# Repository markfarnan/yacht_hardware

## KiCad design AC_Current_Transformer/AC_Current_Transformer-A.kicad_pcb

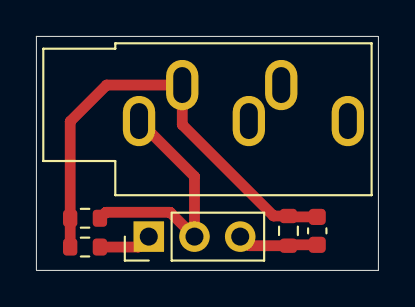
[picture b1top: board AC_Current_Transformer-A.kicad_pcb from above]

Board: 2 copper layers, 19.0 x 13.0 mm, 6 parts (0 on the bottom side), 4 nets.

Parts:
C101: CP; C_0603_1608Metric
J101: AudioJack3; Jack_3.5mm_CUI_SJ1-3535NG_Horizontal
J102: Conn_01x03_Male; PinHeader_1x03_P2.54mm_Vertical
R101: 120; R_0603_1608Metric
R102, R103: 12; R_0603_1608Metric

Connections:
+3V3: J102.1, R102.1
GND: C101.2, J102.3, R103.2
unnamed: C101.1, J101.T, R101.2, R102.2, R103.1
unnamed: J101.S, J102.2, R101.1

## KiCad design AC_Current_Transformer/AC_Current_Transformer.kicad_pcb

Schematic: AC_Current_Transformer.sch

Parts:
C101: 10uf/50V; C_1206_3216Metric; LCSC C13585
C102, C103: 33pF; C_0402_1005Metric; LCSC C1562
C104, C105: 33pF/50V; C_0603_1608Metric; LCSC C1663
FB101, FB102: GZ2012D101TF; L_0805_2012Metric; LCSC C1015
J101: Interface; PinHeader_1x07_P2.54mm_Horizontal
J102: AudioJack3; Jack_3.5mm_CUI_SJ1-3535NG_Horizontal
J103: Conn_01x02; PinHeader_1x02_P2.54mm_Horizontal
R101: 120; R_0603_1608Metric
R102, R103: 10k; R_0603_1608Metric

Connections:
+3V3: J101.1, R102.1
/GPIO: C103.1, FB101.2, J101.3, R101.1
GND: C101.2, C102.2, C103.2, C104.2, C105.2, J101.2, J101.7, R103.2
unnamed: C101.1, C102.1, FB102.2, R101.2, R102.2, R103.1
unnamed: C104.1, FB101.1, J102.T, J103.2
unnamed: C105.1, FB102.1, J102.S, J103.1

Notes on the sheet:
Standard ‘Module’ 7 Pin header Pins 1 & 2 (+3V3, GND) never change Pin 3 is normally the ‘I/O’ pin for the module (i.e. connects to the GPIO of SH32) Other pins depend on application

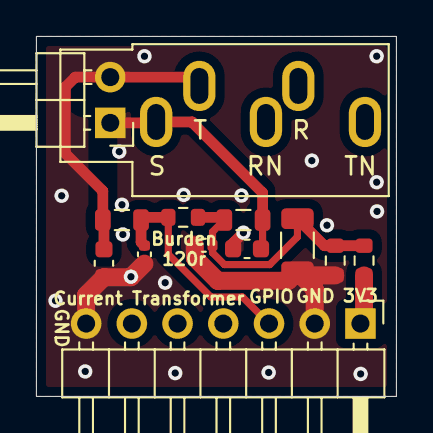
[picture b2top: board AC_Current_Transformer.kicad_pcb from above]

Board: 2 copper layers, 20.0 x 20.0 mm, 13 parts (0 on the bottom side), 6 nets.

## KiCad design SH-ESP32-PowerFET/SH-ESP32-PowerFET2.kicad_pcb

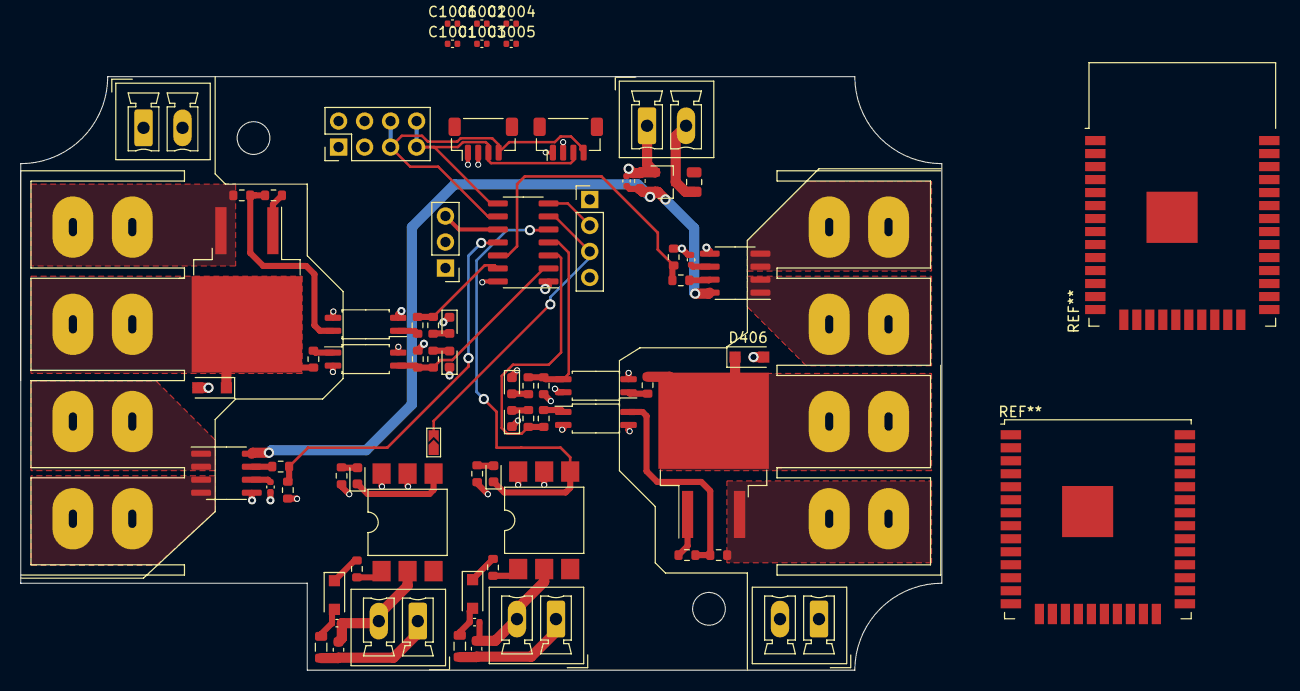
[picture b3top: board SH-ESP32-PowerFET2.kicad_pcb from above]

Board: 4 copper layers, 90.0 x 58.0 mm, 76 parts (0 on the bottom side), 55 nets.

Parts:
C301, C303: 33pF; C_0402_1005Metric
C302, C304: 33pF/50V; C_0603_1608Metric
C501: 2.2uF/50V; C_0805_2012Metric
C502, C503: 1nF; C_0402_1005Metric
C504: 2.2uF/16V; C_0603_1608Metric
C505, C1001, C1002, C1003, C1004, C1005, C1006: 100nF; C_0402_1005Metric
D301, D303, D403, D404: GREEN LED; LED_0603_1608Metric
D302, D304, D405, D406: SM4007PL; D_SOD-123F
D401, D402: BLUE LED; LED_0603_1608Metric
FB301, FB302: GZ2012D101TF; L_0805_2012Metric
H1001, H1002: MountingHole; MountingHole_3.2mm_M3_Unplated
J101: I2C; PinHeader_2x04_P2.54mm_Vertical
J102: 1-WIRE; PinHeader_1x04_P2.54mm_Vertical
J103: UPDI; PinHeader_1x03_P2.54mm_Vertical
J104, J107: QWIIC; JST_SH_BM04B-SRSS-TB_1x04-1MP_P1.00mm_Vertical
J105, J106: DBT50G-9.5-4P; Connector_9.5mm_ScrewTerminal_4-Reversable
J301, J302: OptoIn; PhoenixContact_MCV_1,5_2-G-3.81_1x02_P3.81mm_Vertical
J401, J402, J501: VIN; PhoenixContact_MCV_1,5_2-G-3.81_1x02_P3.81mm_Vertical
JP101: Jumper_NO_Small; SolderJumper-2_P1.3mm_Open_TrianglePad_Narrow
Q401, Q402: IRF5210STRLPBF; TO-263-2
R301, R303, R411, R412: 1k; R_0603_1608Metric
R302, R304: 3k; R_0603_1608Metric
R401, R402, R407, R408: 2k; R_0603_1608Metric
R403, R405, R413, R414: 2.2k; R_0603_1608Metric
R404, R406: 220R; R_0603_1608Metric
R409, R410, R501, R502: 10k; R_0603_1608Metric
R503, R504: 470; R_0603_1608Metric
U101: ATtiny1614-SS; SOIC-14_3.9x8.7mm_P1.27mm
U301, U302: H11L1SR2M; SMDIP-6_W9.53mm
U401, U402, U403, U404: EL3H7(C)(TA)-G; SOP-4_4.4x2.6mm_P1.27mm
U501: H7550-H#; SOT-23
U502, U503: ACS712ELCTR-20A-T; SOIC-8_3.9x4.9mm_P1.27mm

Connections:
+3V3: C1001.2, C1002.2, C1003.2, C1004.2, C1005.2, C1006.2, J101.3, J101.4, J102.1, J103.1, J104.2, J107.2, R301.1, R303.1, U101.1, U301.6, U302.6, U403.4, U404.4
+5V: C504.1, C505.2, U501.2, U502.8, U503.8
/Opto Input/ISO_GND_1: C301.2, C302.2, J301.2, U301.2
/Opto Input/ISO_GND_2: C303.2, C304.2, J302.2, U302.2
/Opto Input/ISO_IN_1: C302.1, FB301.1, J301.1
/Opto Input/ISO_IN_2: C304.1, FB302.1, J302.1
/RxD: J102.3, JP101.2, U101.6
/SCL: J101.5, J101.6, J104.4, J107.4, U101.9
/SDA: J101.7, J101.8, J104.3, J107.3, U101.8
/TxD_1-WIRE: J102.2, U101.7
/UPDI: J103.3, U101.10
FETOUT_01: R401.1, R404.2, U101.13
FETOUT_02: R402.1, R406.2, U101.3
FETSENSE_01: R403.2, R407.1, U101.2, U403.3
FETSENSE_02: R405.2, R408.1, U101.4, U404.3
GND: C501.2, C502.2, C503.2, C504.2, C505.1, C1001.1, C1002.1, C1003.1, C1004.1, C1005.1, C1006.1, D401.1, D402.1, D403.1, D404.1, J101.1, J101.2, J102.4, J103.2, J104.1, J107.1, J501.1, R403.1, R405.1, R501.2, R502.2, U101.14, U301.5, U302.5, U401.2, U402.2, U501.1, U502.5, U503.5
GND1: D405.2, J402.1, J402.2, U401.3, U403.2
GND2: D406.2, J401.1, J401.2, U402.3, U404.2
unnamed: C301.1, D302.2, FB301.2
unnamed: C303.1, D304.2, FB302.2
unnamed: C501.1, J501.2, U501.3
unnamed: C502.1, U502.6
unnamed: C503.1, U503.6
unnamed: D301.2, R301.2
unnamed: D302.1, R302.1
unnamed: D303.2, R303.2
unnamed: D304.1, R304.1
unnamed: D401.2, R401.2
unnamed: D402.2, R402.2
unnamed: D403.2, R407.2
unnamed: D404.2, R408.2
unnamed: Q401.1, R411.1
unnamed: Q402.1, R412.1
unnamed: R302.2, U301.1
unnamed: R304.2, U302.1
unnamed: R404.1, U401.1
unnamed: R406.1, U402.1
unnamed: R409.2, R411.2, U401.4
unnamed: R410.2, R412.2, U402.4
unnamed: R413.2, U403.1
unnamed: R414.2, U404.1
unnamed: R503.1, U502.7
unnamed: R504.1, U503.7
OPTO_IN_1: D301.1, U101.5, U301.4
OPTO_IN_2: D303.1, JP101.1, U302.4
SENSE_VINeg_01: J105.4, U502.3, U502.4
SENSE_VINeg_02: J106.4, U503.3, U503.4
SENSE_VIPos_01: J105.3, U502.1, U502.2
SENSE_VIPos_02: J106.3, U503.1, U503.2
VIN_01: J105.1, Q401.3, R409.1
VIN_02: J106.1, Q402.3, R410.1
VOUT_01: D405.1, J105.2, Q401.2, R413.1
VOUT_02: D406.1, J106.2, Q402.2, R414.1
VSENSE_01: R501.1, R503.2, U101.11
VSENSE_02: R502.1, R504.2, U101.12

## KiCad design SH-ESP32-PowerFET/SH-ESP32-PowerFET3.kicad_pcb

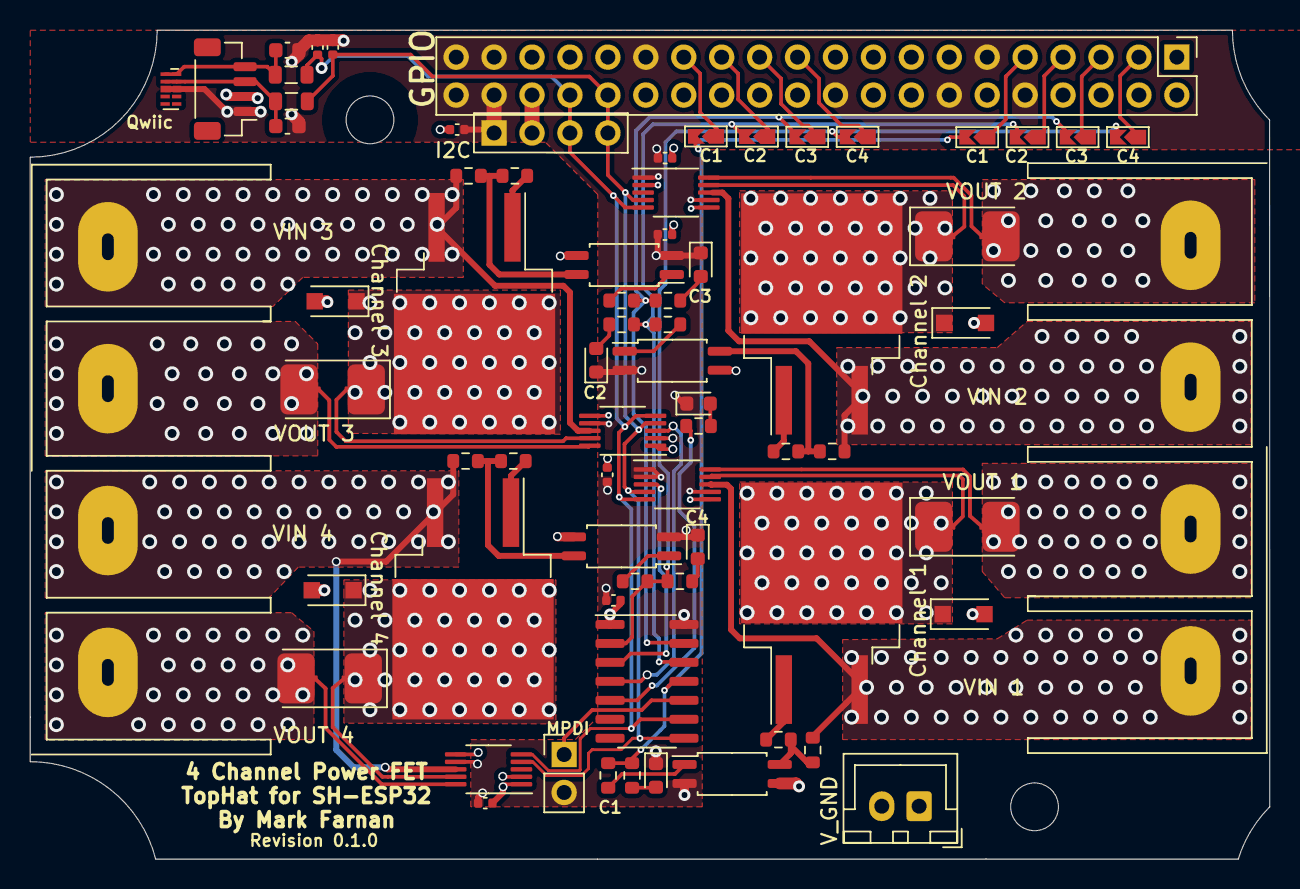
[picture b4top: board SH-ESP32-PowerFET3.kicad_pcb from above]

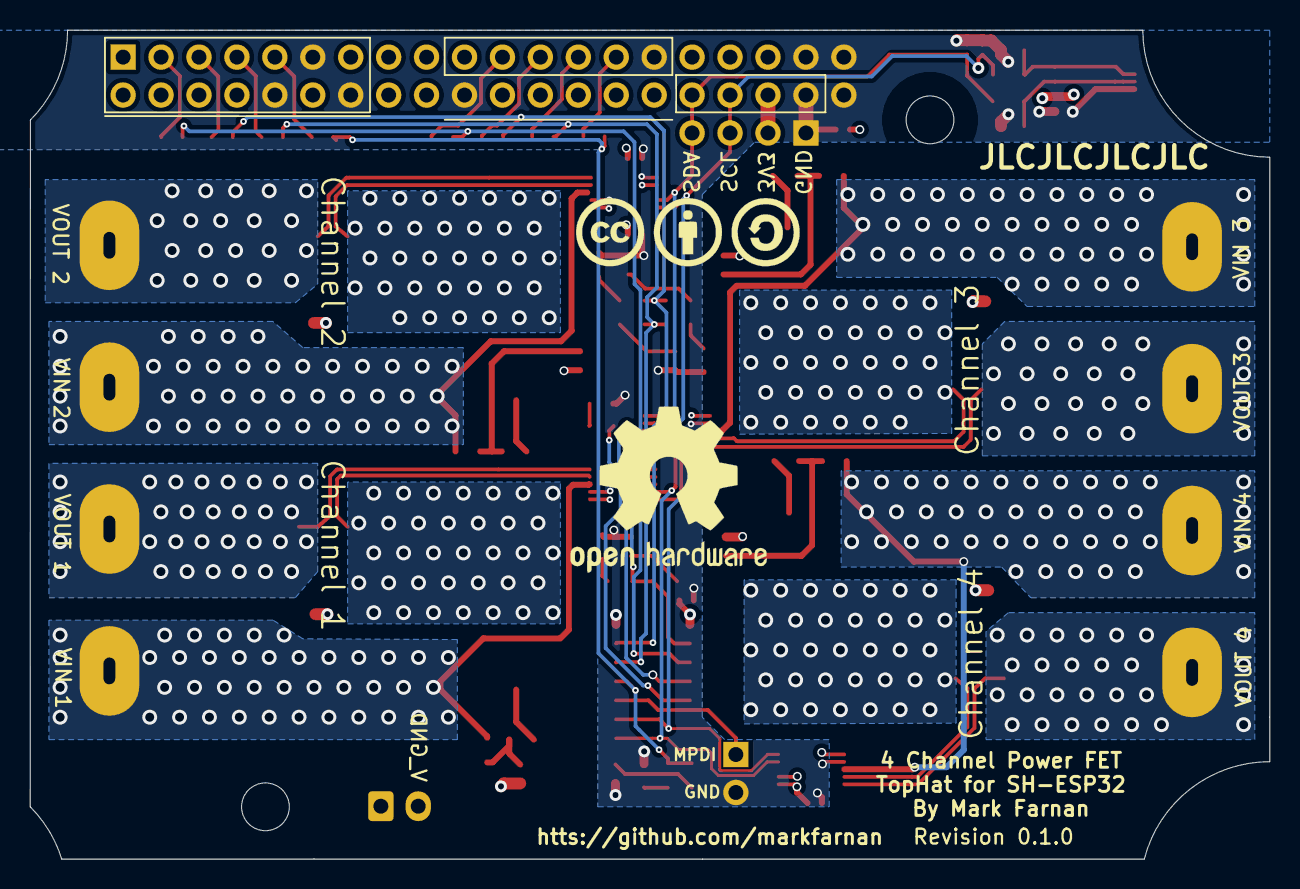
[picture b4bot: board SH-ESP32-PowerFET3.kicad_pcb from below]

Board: 4 copper layers, 83.0 x 55.5 mm, 75 parts (2 on the bottom side), 52 nets.

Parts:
C102, C103: 33pF/50V; C_0603_1608Metric
C105, C106: 33pF; C_0402_1005Metric
C201, C202, C203, C204, C205, C206: 100nF; C_0402_1005Metric
D101: RED LED; LED_0603_1608Metric
D301, D302, D303, D307: BLUE LED; LED_0603_1608Metric
D304, D305, D306, D308: SM4007PL; D_SOD-123F
FB102, FB103: GZ2012D101TF; L_0805_2012Metric
H201, H202: MountingHole; MountingHole_3.2mm_M3_Unplated
J101: DBT50G-9.5-4P; Connector_9.5mm_ScrewTerminal_4
J102: DBT50G-9.5-2P; Connector_9.5mm_ScrewTerminal_4
J103: GPIO; PinHeader_2x20_P2.54mm_Vertical
J104: Qwiic; JST_SH_BM04B-SRSS-TB_1x04-1MP_P1.00mm_Vertical
J105: MPDI; PinHeader_1x02_P2.54mm_Vertical
J106: Conn_01x04; PinHeader_1x04_P2.54mm_Vertical-ShrunkCY
J301: VIN_GND1; JST_XH_B2B-XH-A_1x02_P2.50mm_Vertical
JP101, JP102, JP103, JP104, JP105, JP106, JP107, JP108: Solder Jumper; SolderJumper-2_P1.3mm_Open_TrianglePad_Narrow
LOGO_CC: LOGO; cc-by-sa_silkscreen
OSHW: OSHW-Logo2_14.6x12mm_SilkScreen
Q301, Q302, Q303, Q304: IRF5210STRLPBF; TO-263-2
R101, R301, R302, R303, R316: 2k; R_0603_1608Metric
R304, R305, R306, R317: 220R; R_0603_1608Metric
R307, R308, R309, R318: 10k; R_0603_1608Metric
R310, R311, R312, R319: 1k; R_0603_1608Metric
R313, R314, R315, R320: 0.002ohm/3W; D_2512_Shunt
U101: ATtiny1614-SSNR; SOIC-14_3.9x8.7mm_P1.27mm
U301, U302, U303, U307: EL3H7(C)(TA)-G; SOP-4_4.4x2.6mm_P1.27mm
U304, U305, U306, U308: INA226AIDGSR; VSSOP-10_3x3mm_P0.5mm
U701: RCLAMP0524P-N; Diodes_UDFN-10_1.0x2.5mm_P0.5mm

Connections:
+3V3: C201.2, C202.2, C203.2, C204.2, C205.2, C206.2, J103.13, J103.19, J103.35, J103.36, J104.2, J106.2, U101.1, U304.1, U304.6, U305.2, U305.6, U306.6, U308.1, U308.2, U308.6
/FET/VOUT1: D306.1, Q303.2, R315.1, R315.2, U306.9
/FET/VOUT2: D305.1, Q302.2, R314.1, R314.2, U305.9
/FET/VOUT3: D304.1, Q301.2, R313.1, R313.2, U304.9
/FET/VOUT4: D308.1, Q304.2, R320.1, R320.2, U308.9
/IO12: J103.21, JP108.1
/IO13: J103.25, JP106.1
/IO14: J103.23, JP107.1
/IO15: J103.27, JP105.1
/IO18: J103.5, JP103.1
/IO21: J103.3, JP104.1
/IO26: J103.7, JP102.1
/IO27: J103.9, JP101.1
/SCL_CONN: C103.1, FB103.1, J104.4, U701.1, U701.10
/SDA_CONN: C102.1, FB102.1, J104.3, U701.2, U701.9
ALERT1: U101.3, U306.3
ALERT4: U101.4, U304.3
FETOUT_01: JP101.2, JP105.2, R303.1, R306.2, U101.11
FETOUT_02: JP102.2, JP106.2, R302.1, R305.2, U101.12
FETOUT_03: JP103.2, JP107.2, R301.1, R304.2, U101.13
FETOUT_04: JP104.2, JP108.2, R316.1, R317.2, U101.2
GND: C102.2, C103.2, C105.2, C106.2, C201.1, C202.1, C203.1, C204.1, C205.1, C206.1, D101.1, D301.1, D302.1, D303.1, D307.1, J103.10, J103.11, J103.14, J103.20, J103.29, J103.37, J103.38, J103.39, J103.40, J104.1, J105.2, J106.1, U101.14, U301.2, U302.2, U303.2, U304.2, U304.7, U305.1, U305.7, U306.1, U306.2, U306.7, U307.2, U308.7, U701.3, U701.8
GND1: D304.2, D305.2, D306.2, D308.2, J301.2, U301.3, U302.3, U303.3, U307.3
unnamed: D101.2, R101.2
unnamed: D301.2, R301.2
unnamed: D302.2, R302.2
unnamed: D303.2, R303.2
unnamed: D307.2, R316.2
unnamed: J105.1, U101.10
unnamed: Q301.1, R310.1
unnamed: Q302.1, R311.1
unnamed: Q303.1, R312.1
unnamed: Q304.1, R319.1
unnamed: R101.1, U101.5
unnamed: R304.1, U301.1
unnamed: R305.1, U302.1
unnamed: R306.1, U303.1
unnamed: R307.2, R310.2, U301.4
unnamed: R308.2, R311.2, U302.4
unnamed: R309.2, R312.2, U303.4
unnamed: R317.1, U307.1
unnamed: R318.2, R319.2, U307.4
SCL: C106.1, FB103.2, J103.34, J106.3, U101.9, U304.5, U305.5, U306.5, U308.5
SDA: C105.1, FB102.2, J103.32, J106.4, U101.8, U304.4, U305.4, U306.4, U308.4
VIN_01: J101.1, Q303.3, R309.1, U306.8
VIN_02: J101.3, Q302.3, R308.1, U305.8
VIN_03: J102.1, Q301.3, R307.1, U304.8
VIN_04: J102.3, Q304.3, R318.1, U308.8
VOUT_01: J101.2, R315.3, R315.4, U306.10
VOUT_02: J101.4, R314.3, R314.4, U305.10
VOUT_03: J102.2, R313.3, R313.4, U304.10
VOUT_04: J102.4, R320.3, R320.4, U308.10

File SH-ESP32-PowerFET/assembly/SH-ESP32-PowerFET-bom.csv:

Comment,Designator,Footprint,LCSC
"33pF/50V","C102,C103","Capacitor_SMD:C_0603_1608Metric","C1663"
"33pF","C105,C106","Capacitor_SMD:C_0402_1005Metric","C1562"
"100nF","C201,C202,C203,C204,C205,C206","Capacitor_SMD:C_0402_1005Metric","C1525"
"RED LED","D101","LED_SMD:LED_0603_1608Metric","C72038"
"BLUE LED","D301,D302,D303,D307","LED_SMD:LED_0603_1608Metric","C72041"
"SM4007PL","D304,D305,D306,D308","Diode_SMD:D_SOD-123F","C64898"
"GZ2012D101TF","FB102,FB103","Inductor_SMD:L_0805_2012Metric","C1015"
"MountingHole","H201,H202","SH-ESP32:MountingHole_3.2mm_M3_Unplated",""
"DBT50G-9.5-4P","J101","yacht_hardware:Connector_9.5mm_ScrewTerminal_4","C395960"
"DBT50G-9.5-2P","J102","yacht_hardware:Connector_9.5mm_ScrewTerminal_4","C395960"
"GPIO","J103","Connector_PinHeader_2.54mm:PinHeader_2x20_P2.54mm_Vertical","C358701"
"Qwiic","J104","Connector_JST:JST_SH_BM04B-SRSS-TB_1x04-1MP_P1.00mm_Vertical","C145961"
"MPDI","J105","Connector_PinHeader_2.54mm:PinHeader_1x02_P2.54mm_Vertical","C376075"
"Conn_01x04","J106","yacht_hardware:PinHeader_1x04_P2.54mm_Vertical-ShrunkCY","C358686"
"VIN_GND1","J301","Connector_JST:JST_XH_B2B-XH-A_1x02_P2.50mm_Vertical",""
"Solder Jumper","JP101,JP102,JP103,JP104,JP105,JP106,JP107,JP108","yacht_hardware:SolderJumper-2_P1.3mm_Open_TrianglePad_Narrow",""
"IRF5210STRLPBF","Q301,Q302,Q303,Q304","Package_TO_SOT_SMD:TO-263-2","C2622"
"2k","R101,R301,R302,R303,R316","Resistor_SMD:R_0603_1608Metric","C22975"
"220R","R304,R305,R306,R317","Resistor_SMD:R_0603_1608Metric","C22962"
"10k","R307,R308,R309,R318","Resistor_SMD:R_0603_1608Metric","C25804"
"1k","R310,R311,R312,R319","Resistor_SMD:R_0603_1608Metric","C21190"
"0.002ohm/3W","R313,R314,R315,R320","yacht_hardware:D_2512_Shunt","C76234"
"ATtiny1614-SSNR","U101","Package_SO:SOIC-14_3.9x8.7mm_P1.27mm","C481364"
"EL3H7(C)(TA)-G","U301,U302,U303,U307","Package_SO:SOP-4_4.4x2.6mm_P1.27mm","C92243"
"INA226AIDGSR","U304,U305,U306,U308","Package_SO:VSSOP-10_3x3mm_P0.5mm","C49851"
"RCLAMP0524P-N","U701","Package_DFN_QFN:Diodes_UDFN-10_1.0x2.5mm_P0.5mm","C316044"

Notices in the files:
SH-ESP32-PowerFET/SH-ESP32-PowerFET2.kicad_pcb:
Sailor Hat for ESP32 is licensed under CC BY-SA 4.0.
